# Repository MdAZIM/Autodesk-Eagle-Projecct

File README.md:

# Autodesk-Eagle-Projecct
Here, pcb design

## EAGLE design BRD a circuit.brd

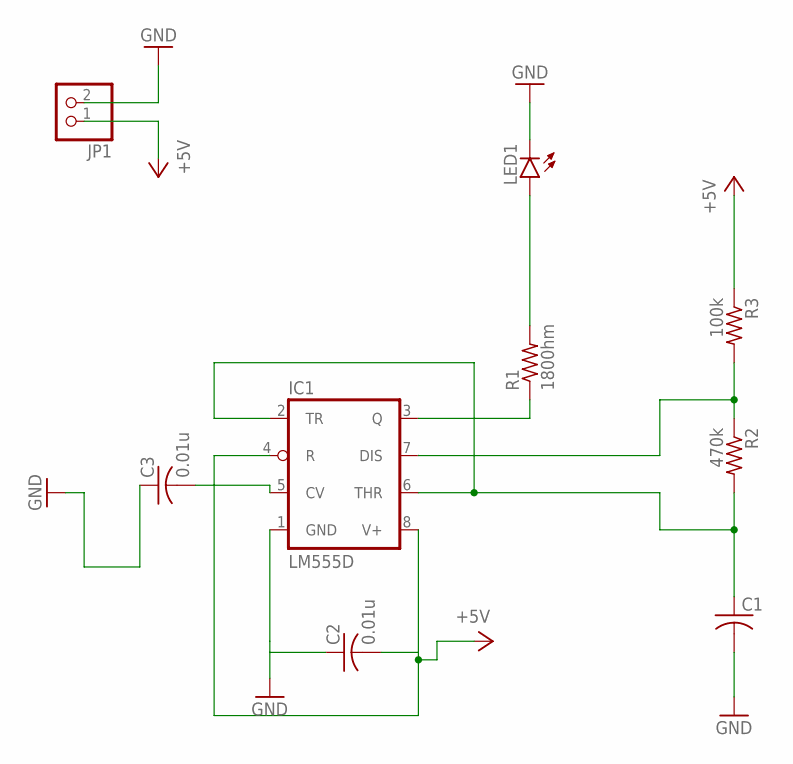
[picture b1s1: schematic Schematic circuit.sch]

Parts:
C1: C-USC0805; C0805
C2, C3: 0.01u; C0805
IC1: LM555D; SO08
JP1: PINHD-1X2; 1X02
LED1: LED5MM
R1: 1800hm; R0805
R2: 470k; R0805
R3: 100k; R0805

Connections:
+5V: C2.2, IC1.4 (R), IC1.8 (V+), JP1.1, R3.1
GND: C1.2, C2.1, C3.1, IC1.1 (GND), JP1.2, LED1.K (C)
unnamed: IC1.3 (Q), R1.1
unnamed: IC1.7 (DIS), R2.1, R3.2
unnamed: C1.1, IC1.2 (TR), IC1.6 (THR), R2.2
unnamed: C3.2, IC1.5 (CV)
unnamed: LED1.A, R1.2

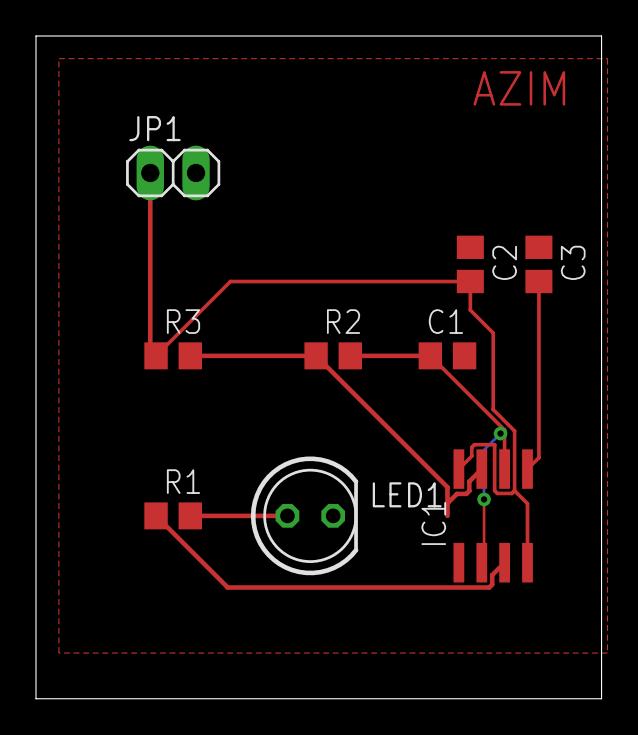
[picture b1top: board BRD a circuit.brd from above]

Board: 2 copper layers, 31.4 x 36.8 mm, 9 parts (0 on the bottom side), 7 nets.

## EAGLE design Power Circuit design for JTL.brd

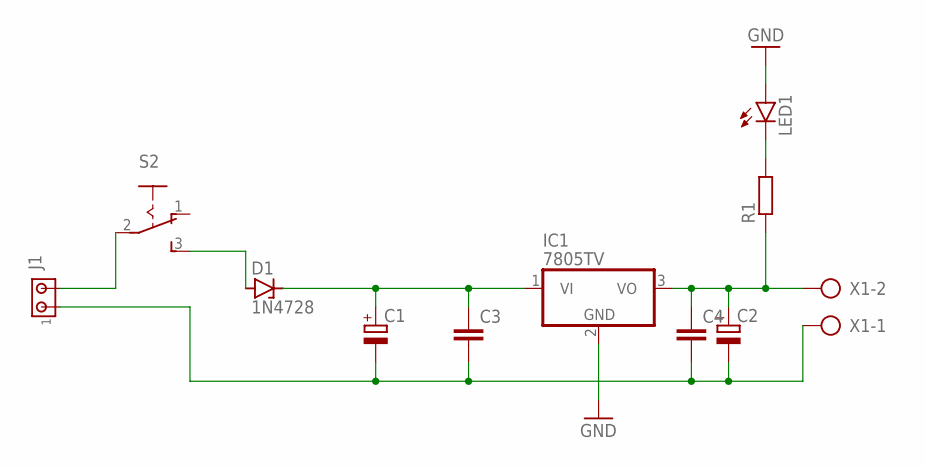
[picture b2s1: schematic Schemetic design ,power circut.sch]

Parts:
C1, C2: CPOL-EUE2.5-6; E2,5-6
C3, C4: C-EU025-040X050; C025-040X050
D1: 1N4728; DO41Z10
IC1: 7805TV; TO220V
J1: MTA02-100; 10X02MTA
LED1: LED5MM
R1: R-EU_0204/7; 0204/7
S2: 255SB
X1: AK300/2

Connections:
GND: LED1.A
unnamed: C1.+, C3.1, D1.C, IC1.1 (VI)
unnamed: C1.-, C2.-, C3.2, C4.2, IC1.2 (GND), J1.1, X1.1
unnamed: C2.+, C4.1, IC1.3 (VO), R1.1, X1.2
unnamed: D1.A, S2.3 (S)
unnamed: J1.2, S2.2
unnamed: LED1.K (C), R1.2

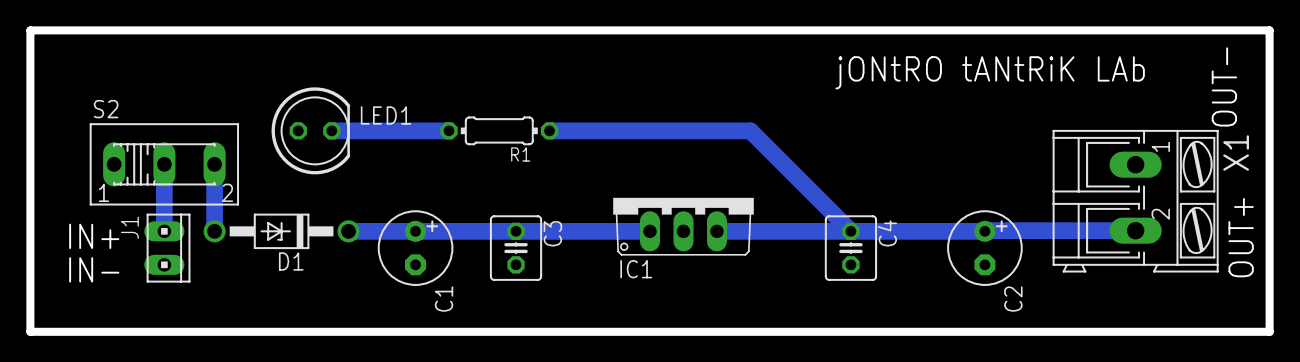
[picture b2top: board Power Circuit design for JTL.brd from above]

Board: 2 copper layers, 94.0 x 22.9 mm, 11 parts (0 on the bottom side), 6 nets.

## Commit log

2019-07-24 Add files via upload
    Schemetic design ,power circut
